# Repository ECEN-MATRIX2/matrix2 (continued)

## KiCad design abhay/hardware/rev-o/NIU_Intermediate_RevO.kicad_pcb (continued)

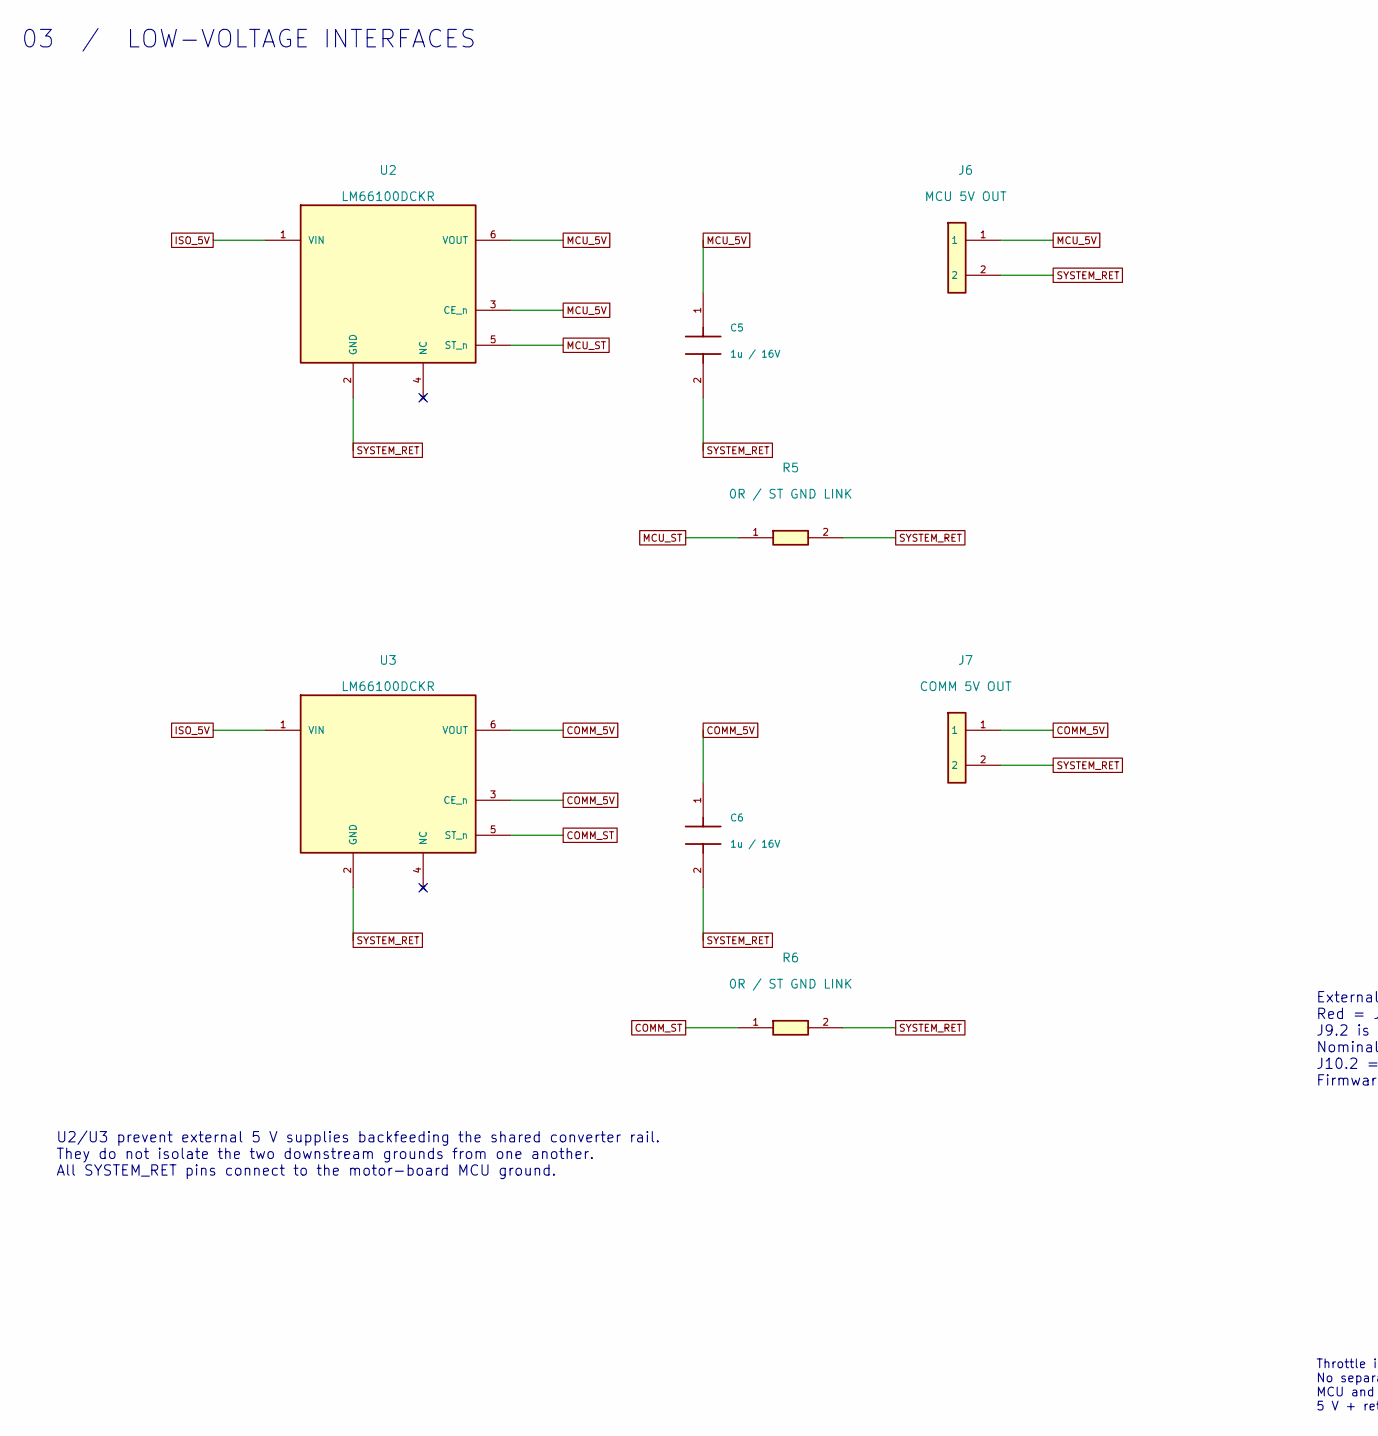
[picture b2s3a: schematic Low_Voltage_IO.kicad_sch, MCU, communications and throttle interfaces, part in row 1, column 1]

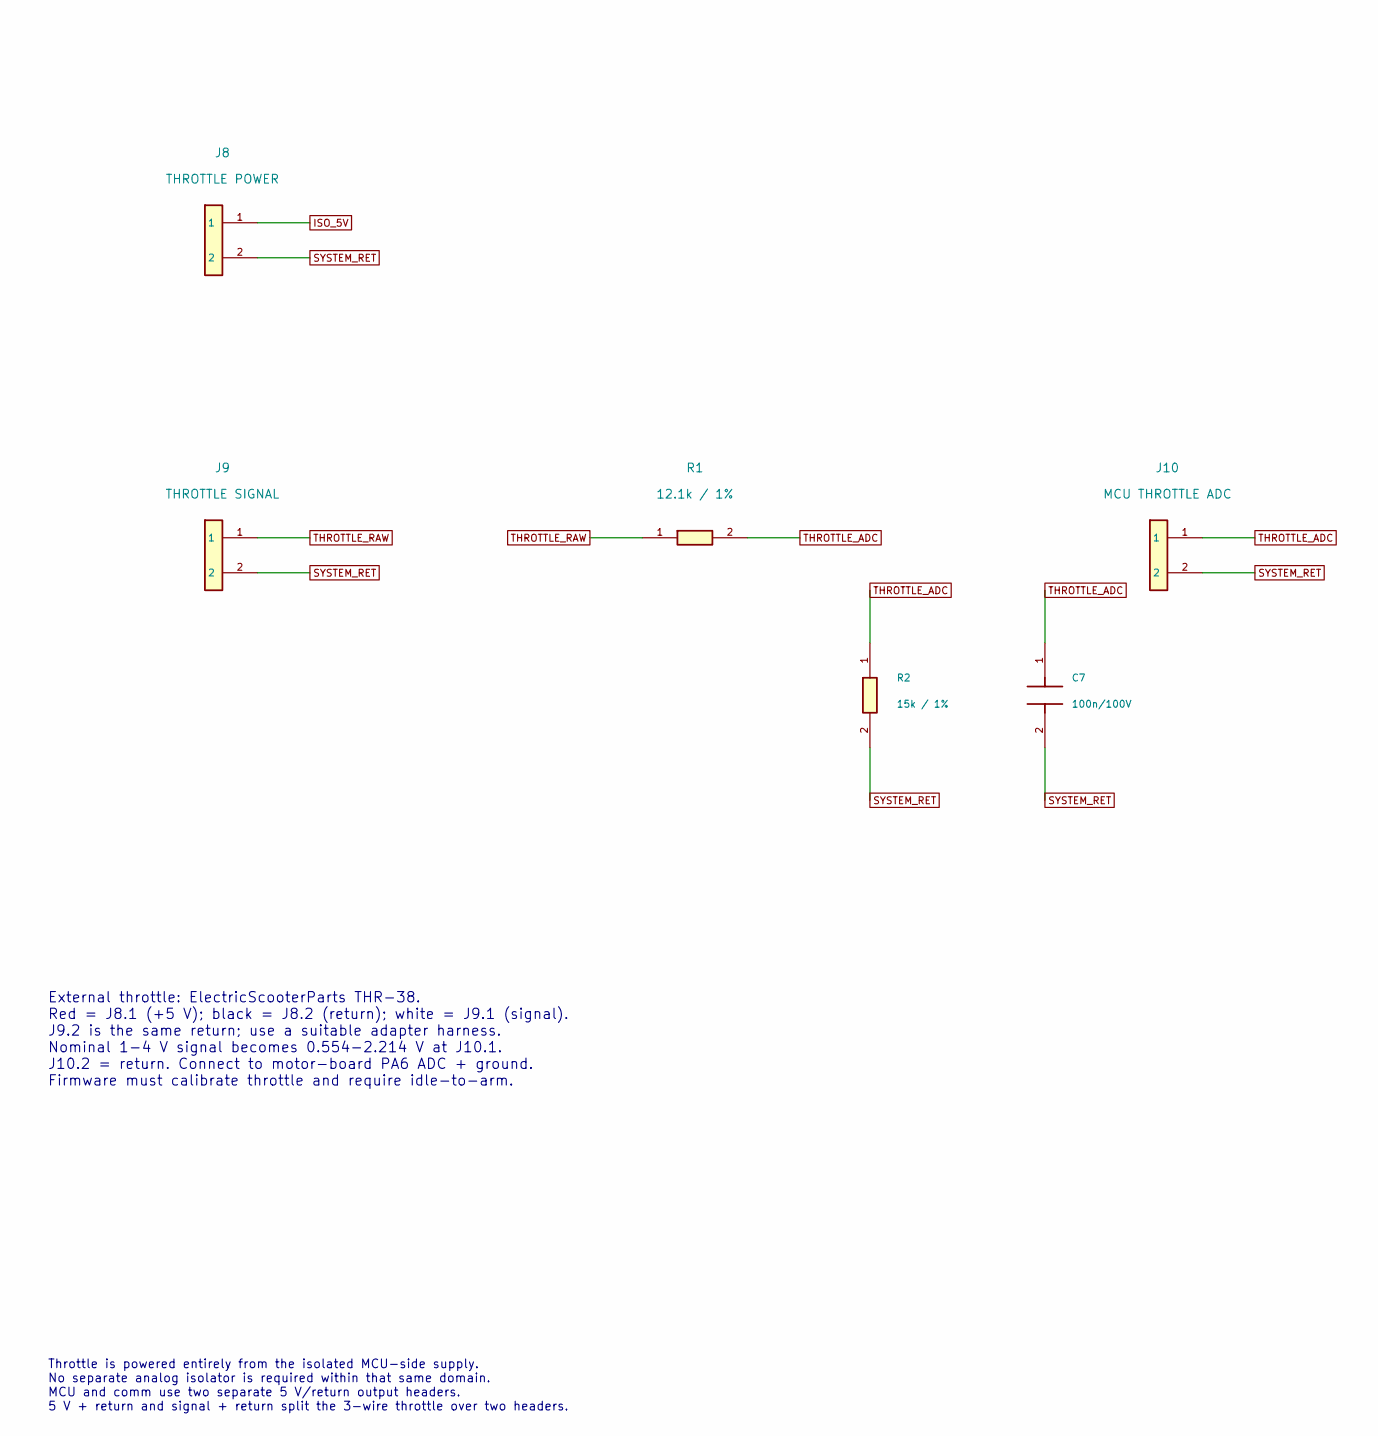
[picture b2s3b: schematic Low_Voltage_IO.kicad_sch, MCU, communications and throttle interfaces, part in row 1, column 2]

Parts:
C5, C6: 1u / 16V; C_0805_2012Metric; Rating X7R 0805, 16V; MPN GRM21BR71C105KA01L; Mouser 81-GRM40X105K16L
C7: 100n/100V; C_0805_2012Metric; Rating X7R, 10%, 0805; MPN C2012X7R2A104K125AA; Mouser 810-C2012X7R2A104K
J6: MCU 5V OUT; PinHeader_1x02_P2.54mm_Vertical; Rating 3A header / LV signals; MPN M20-9990245; Mouser 855-M20-9990245
J7: COMM 5V OUT; PinHeader_1x02_P2.54mm_Vertical; Rating 3A header / LV signals; MPN M20-9990245; Mouser 855-M20-9990245
J8: THROTTLE POWER; PinHeader_1x02_P2.54mm_Vertical; Rating 3A header / LV signals; MPN M20-9990245; Mouser 855-M20-9990245
J9: THROTTLE SIGNAL; PinHeader_1x02_P2.54mm_Vertical; Rating 3A header / LV signals; MPN M20-9990245; Mouser 855-M20-9990245
J10: MCU THROTTLE ADC; PinHeader_1x02_P2.54mm_Vertical; Rating 3A header / LV signals; MPN M20-9990245; Mouser 855-M20-9990245
R1: 12.1k / 1%; R_0805_2012Metric; Rating 1% 0.125W; MPN RC0805FR-0712K1L; Mouser 603-RC0805FR-0712K1L
R2: 15k / 1%; R_0805_2012Metric; Rating 1% 0.125W; MPN RC0805FR-0715KL; Mouser 603-RC0805FR-0715KL
R5, R6: 0R / ST GND LINK; R_0805_2012Metric; Rating 0 ohm configuration link; MPN RC0805JR-070RL; Mouser 603-RC0805JR-070RL
U2, U3: LM66100DCKR; SOT-363_SC-70-6; Rating 1.5-5.5V / 1.5A; MPN LM66100DCKR; Mouser 595-LM66100DCKR

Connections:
COMM_5V: C6.1, J7.1, U3.3 (CE_n), U3.6 (VOUT)
COMM_ST: R6.1, U3.5 (ST_n)
ISO_5V: J8.1, U2.1 (VIN), U3.1 (VIN); also elsewhere on the board
MCU_5V: C5.1, J6.1, U2.3 (CE_n), U2.6 (VOUT)
MCU_ST: R5.1, U2.5 (ST_n)
SYSTEM_RET: C5.2, C6.2, C7.2, J6.2, J7.2, J8.2, J9.2, J10.2, R2.2, R5.2, R6.2, U2.2 (GND), U3.2 (GND); also elsewhere on the board
THROTTLE_ADC: C7.1, J10.1, R1.2, R2.1
THROTTLE_RAW: J9.1, R1.1

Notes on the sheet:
03 / LOW-VOLTAGE INTERFACES
U2/U3 prevent external 5 V supplies backfeeding the shared converter rail. They do not isolate the two downstream grounds from one another. All SYSTEM_RET pins connect to the motor-board MCU ground.
External throttle: ElectricScooterParts THR-38. Red = J8.1 (+5 V); black = J8.2 (return); white = J9.1 (signal). J9.2 is the same return; use a suitable adapter harness. Nominal 1-4 V signal becomes 0.554-2.214 V at J10.1. J10.2 = return. Connect to motor-board PA6 ADC + ground. Firmware must calib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
Throttle is powered entirely from the isolated MCU-side supply. No separate analog isolator is required within that same domain. MCU and comm use two separate 5 V/return output headers. 5 V + return and signal + return split the 3-wire throttle over two headers.

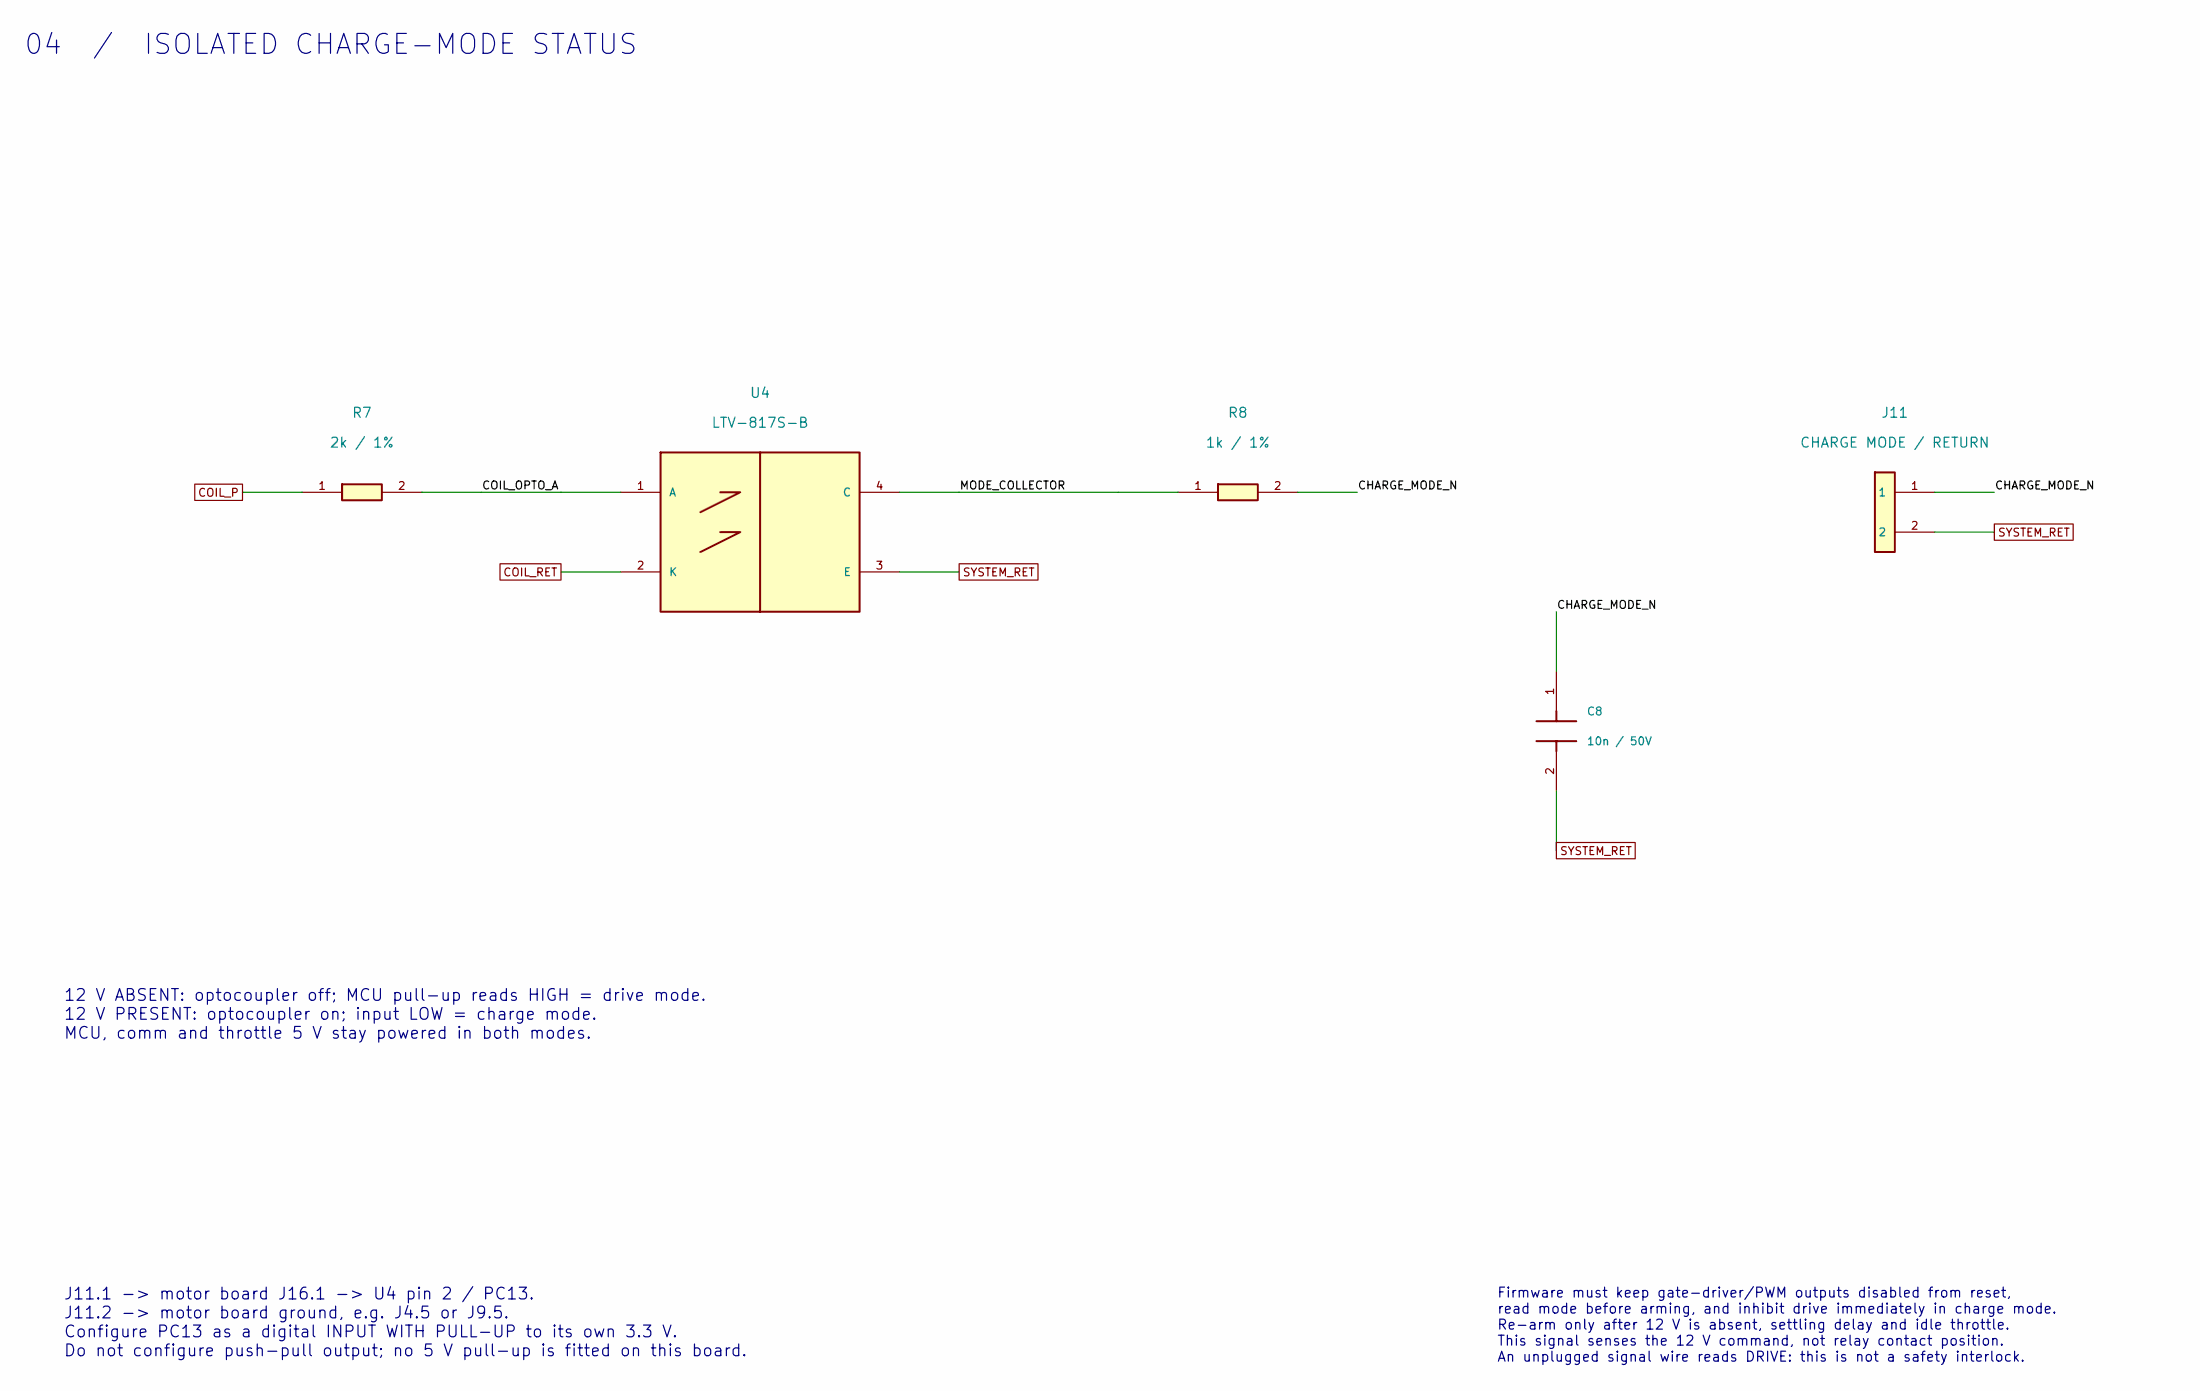
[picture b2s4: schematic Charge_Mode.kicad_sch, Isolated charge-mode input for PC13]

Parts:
C8: 10n / 50V; C_0805_2012Metric; Rating X7R, 10%, 0805; MPN C0805C103K5RACTU; Mouser 80-C0805C103K5R
J11: CHARGE MODE / RETURN; PinHeader_1x02_P2.54mm_Vertical; Rating 3A header / LV signals; MPN M20-9990245; Mouser 855-M20-9990245
R7: 2k / 1%; R_0805_2012Metric; Rating 1% 0.125W; MPN RC0805FR-072KL; Mouser 603-RC0805FR-072KL
R8: 1k / 1%; R_0805_2012Metric; Rating 1% 0.125W; MPN RC0805FR-071KL; Mouser 603-RC0805FR-071KL
U4: LTV-817S-B; SMDIP-4_W9.53mm; Rating Optocoupler; CTR 130-260% at 5mA; MPN LTV-817S-B; Mouser 859-LTV-817S-B

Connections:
/Charge Mode/CHARGE_MODE_N: C8.1, J11.1, R8.2
/Charge Mode/COIL_OPTO_A: R7.2, U4.1 (A)
/Charge Mode/MODE_COLLECTOR: R8.1, U4.4 (C)
COIL_P: R7.1; also elsewhere on the board
COIL_RET: U4.2 (K); also elsewhere on the board
SYSTEM_RET: C8.2, J11.2, U4.3 (E); also elsewhere on the board

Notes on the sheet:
04 / ISOLATED CHARGE-MODE STATUS
12 V ABSENT: optocoupler off; MCU pull-up reads HIGH = drive mode. 12 V PRESENT: optocoupler on; input LOW = charge mode. MCU, comm and throttle 5 V stay powered in both modes.
J11.1 -> motor board J16.1 -> U4 pin 2 / PC13. J11.2 -> motor board ground, e.g. J4.5 or J9.5. Configure PC13 as a digital INPUT WITH PULL-UP to its own 3.3 V. Do not configure push-pull output; no 5 V pull-up is fitted on this board.
Firmware must keep gate-driver/PWM outputs disabled from reset, read mode before arming, and inhibit drive immediately in charge mode. Re-arm only after 12 V is absent, settling delay and idle throttle. This signal senses the 12 V command, not relay contact position. An unplugged signal wire reads 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

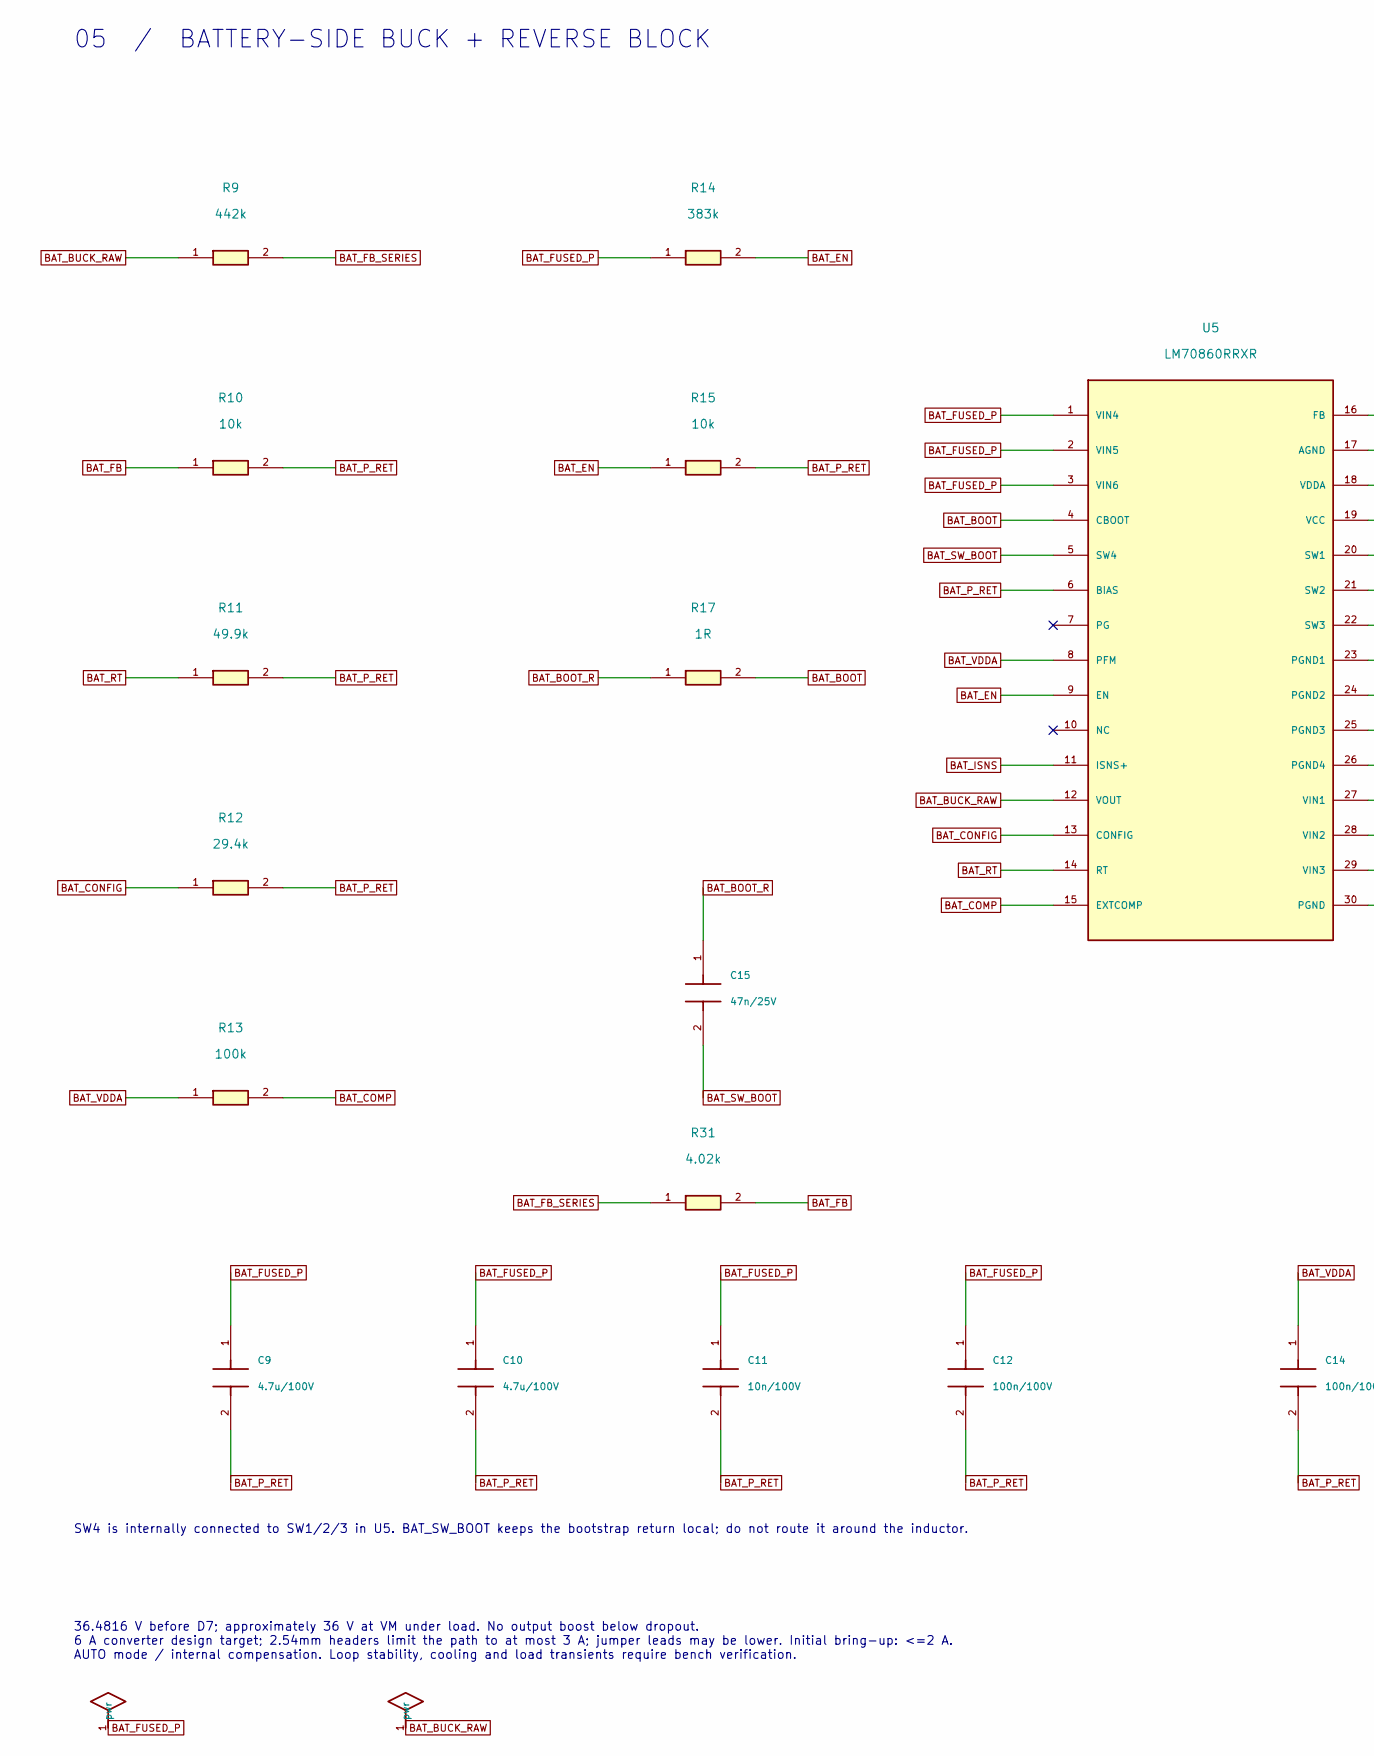
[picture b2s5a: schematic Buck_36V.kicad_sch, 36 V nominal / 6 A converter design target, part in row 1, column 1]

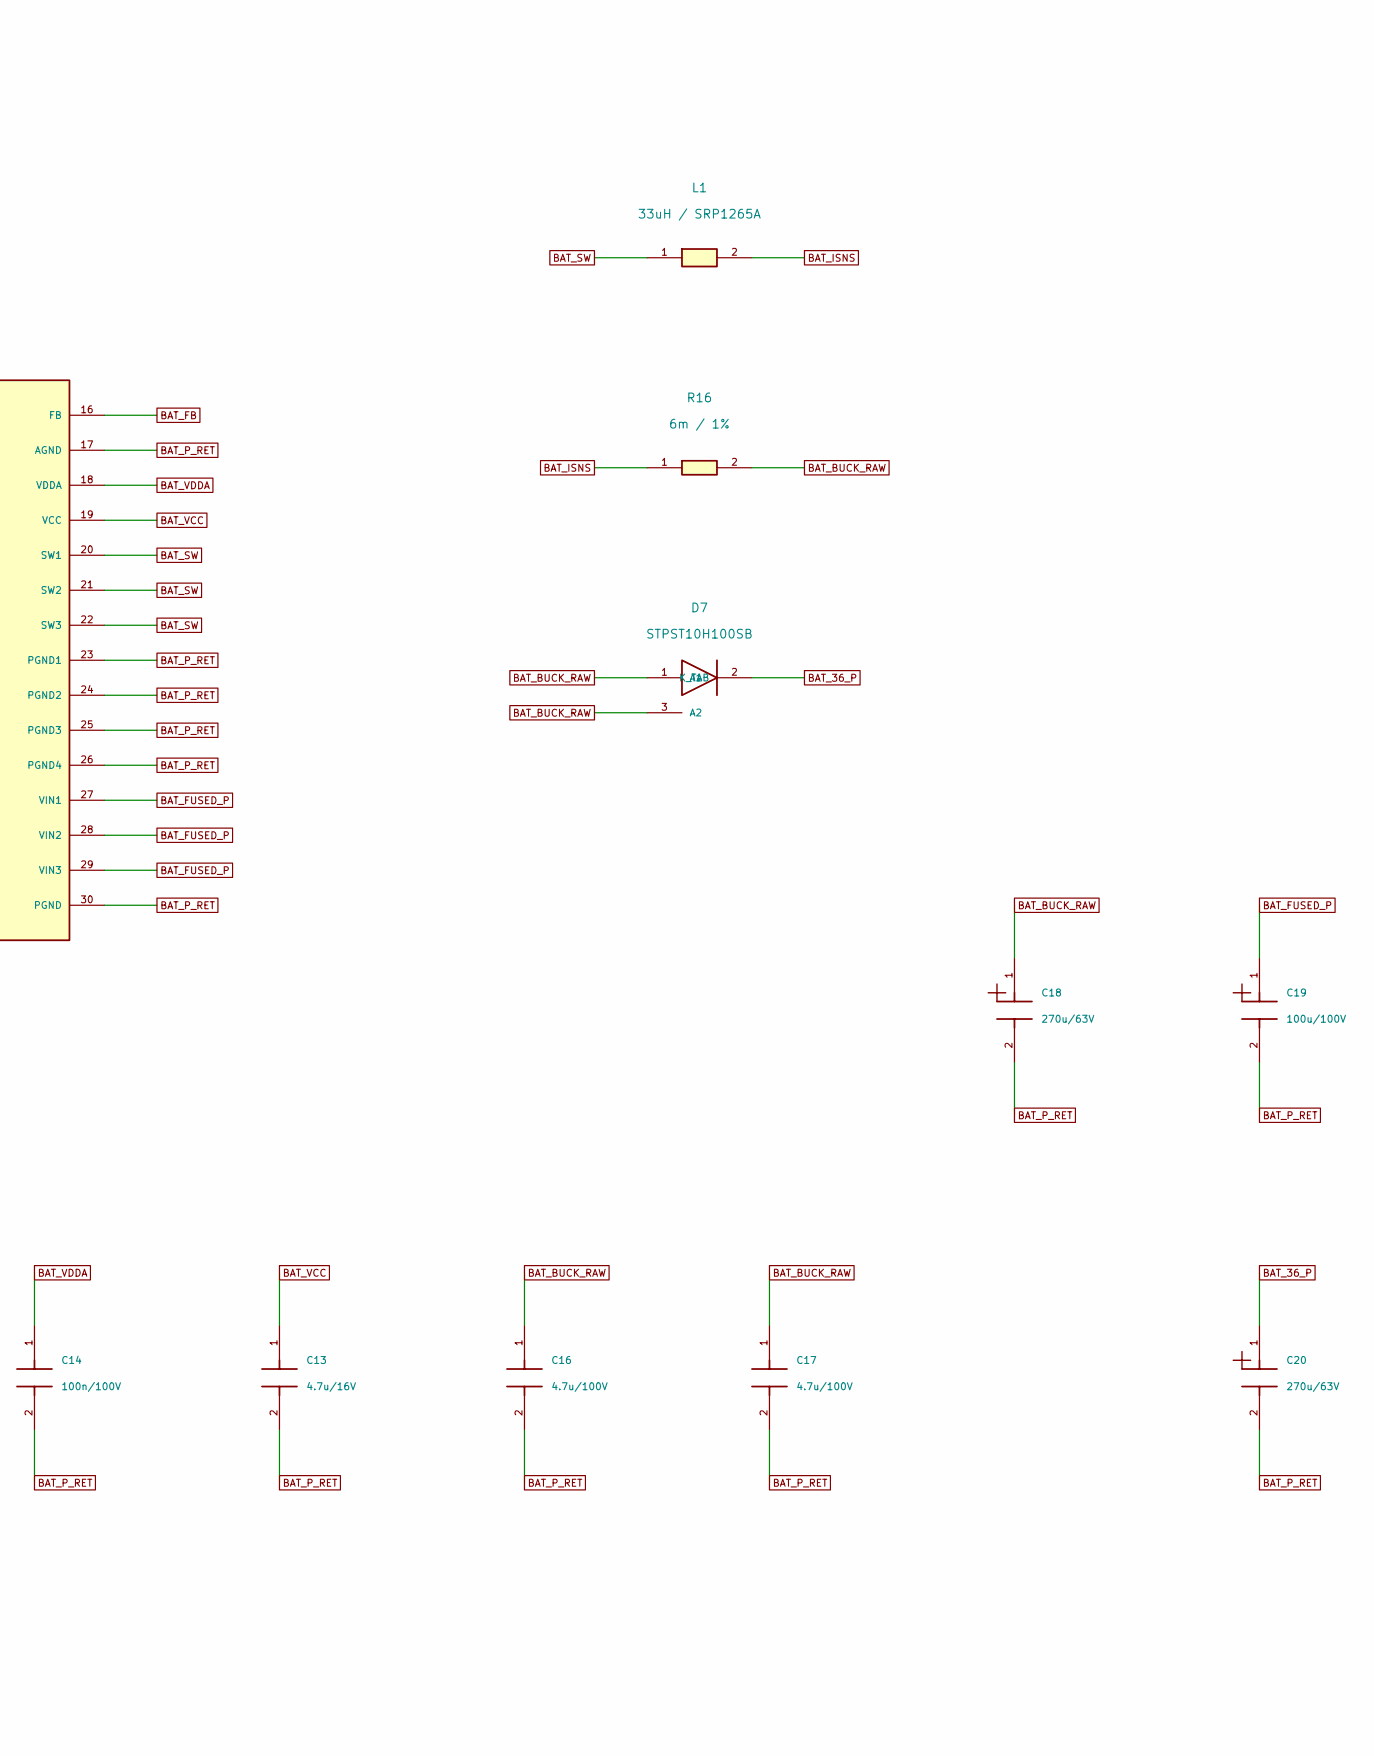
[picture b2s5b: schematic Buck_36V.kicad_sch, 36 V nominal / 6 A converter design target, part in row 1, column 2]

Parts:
C9, C10, C16, C17: 4.7u/100V; TDK_CNC6_1210_Recommended; Rating X7R, 10%, 1210; 3.2 x 2.5 x 2.5 mm; MPN CNC6P1X7R2A475K250AE; Mouser 810-CNC6P1X7R2A475K2
C11: 10n/100V; C_0402_1005Metric; Rating 10nF, 100V, X7S, 0402; MPN C1005X7S2A103K050BB; Mouser 810-C1005X7S2A103K
C12: 100n/100V; C_0603_1608Metric; Rating Verify effective capacitance / ripple c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; MPN GRM188R72A104KA35D; Mouser 81-GRM188R72A104KA35
C13: 4.7u/16V; C_0603_1608Metric; Rating Verify effective capacitance / ripple c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; MPN GRM188R61C475KE11D; Mouser 81-GRM188R61C475KE1D
C14: 100n/100V; C_0603_1608Metric; Rating X7R, 10%, 0603; MPN GRM188R72A104KA35D; Mouser 81-GRM188R72A104KA35
C15: 47n/25V; C_0603_1608Metric; Rating X7R, 10%, 0603; MPN C0603C473K3RACTU; Mouser 80-C0603C473K3R
C18: 270u/63V; CP_Radial_D10.0mm_P5.00mm_H25; Rating 20%; D10 x H25 mm; 5 mm pitch; 0.6 mm l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; MPN EEU-FR1J271L; Mouser 667-EEU-FR1J271L
C19: 100u/100V; CP_Radial_D10.0mm_P5.00mm_H20; Rating Verify effective capacitance / ripple c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; MPN EEU-FR2A101; Mouser 667-EEU-FR2A101
C20: 270u/63V; CP_Radial_D10_P5_H25_PolarityBelow; Rating 20%; D10 x H25 mm; 5 mm pitch; 0.6 mm l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; MPN EEU-FR1J271L; Mouser 667-EEU-FR1J271L
D7: STPST10H100SB; TO-252-3_TabPin2; Rating 100V/10A diode; both anode terminals co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; MPN STPST10H100SB-TR; Mouser 511-STPST10H100SB-TR
L1: 33uH / SRP1265A; Bourns_SRP1265A_13.5x12.5mm; Rating 20%; 8 A Irms; 11 A Isat at 20% drop; D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; MPN SRP1265A-330M; Mouser 652-SRP1265A-330M
R9: 442k; R_0603_1608Metric; Rating 0.1%, 25 ppm/K, 0603; MPN RT0603BRD07442KL; Mouser 603-RT0603BRD07442KL
R10, R15: 10k; R_0603_1608Metric; Rating 0.1% except R17 1%; MPN RT0603BRD0710KL; Mouser 603-RT0603BRD0710KL
R11: 49.9k; R_0603_1608Metric; Rating 0.1% except R17 1%; MPN RT0603BRD0749K9L; Mouser 603-RT0603BRD0749K9L
R12: 29.4k; R_0603_1608Metric; Rating 0.1% except R17 1%; MPN RT0603BRD0729K4L; Mouser 603-RT0603BRD0729K4L
R13: 100k; R_0603_1608Metric; Rating 0.1%, 25 ppm/K, 0603; MPN TNPW0603100KBEEA; Mouser 71-TNPW0603100KBEEA
R14: 383k; R_0603_1608Metric; Rating 0.1% except R17 1%; MPN RT0603BRD07383KL; Mouser 603-RT0603BRD07383KL
R16: 6m / 1%; Vishay_WSL2512_5m_6m9; Rating 1%, 1 W, WSL2512 low-ohm land pattern; MPN WSL25126L000FEA; Mouser 71-WSL25126L000FEA
R17: 1R; R_0603_1608Metric; Rating 0.1% except R17 1%; MPN RC0603FR-071RL; Mouser 603-RC0603FR-071RL
R31: 4.02k; R_0603_1608Metric; Rating 0.1%, 25 ppm/K, 0603; MPN RT0603BRD074K02L; Mouser 603-RT0603BRD074K02L
U5: LM70860RRXR; TI_RRX0029B_6x6; Rating 80V input; 6A target; AUTO; internal co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; MPN LM70860RRXR; Mouser 595-LM70860RRXR

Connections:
BAT_36_P: C20.1, D7.2 (K_TAB); also elsewhere on the board
BAT_BOOT: R17.2, U5.4 (CBOOT)
BAT_BOOT_R: C15.1, R17.1
BAT_BUCK_RAW: C16.1, C17.1, C18.1, D7.1 (A1), D7.3 (A2), R9.1, R16.2, U5.12 (VOUT)
BAT_COMP: R13.2, U5.15 (EXTCOMP)
BAT_CONFIG: R12.1, U5.13 (CONFIG)
BAT_EN: R14.2, R15.1, U5.9 (EN)
BAT_FB: R10.1, R31.2, U5.16 (FB)
BAT_FB_SERIES: R9.2, R31.1
BAT_FUSED_P: C9.1, C10.1, C11.1, C12.1, C19.1, R14.1, U5.1 (VIN4), U5.2 (VIN5), U5.3 (VIN6), U5.27 (VIN1), U5.28 (VIN2), U5.29 (VIN3); also elsewhere on the board
BAT_ISNS: L1.2, R16.1, U5.11 (ISNS+)
BAT_P_RET: C9.2, C10.2, C11.2, C12.2, C13.2, C14.2, C16.2, C17.2, C18.2, C19.2, C20.2, R10.2, R11.2, R12.2, R15.2, U5.6 (BIAS), U5.17 (AGND), U5.23 (PGND1), U5.24 (PGND2), U5.25 (PGND3), U5.26 (PGND4), U5.30 (PGND); also elsewhere on the board
BAT_RT: R11.1, U5.14 (RT)
BAT_SW: L1.1, U5.20 (SW1), U5.21 (SW2), U5.22 (SW3)
BAT_SW_BOOT: C15.2, U5.5 (SW4)
BAT_VCC: C13.1, U5.19 (VCC)
BAT_VDDA: C14.1, R13.1, U5.8 (PFM), U5.18 (VDDA)

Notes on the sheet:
05 / BATTERY-SIDE BUCK + REVERSE BLOCK
36.4816 V before D7; approximately 36 V at VM under load. No output boost below dropout. 6 A converter design target; 2.54mm headers limit the path to at most 3 A; jumper leads may be lower. Initial bring-up: <=2 A. AUTO mode / internal compensation. Loop stability, cooling and load transients requ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
SW4 is internally connected to SW1/2/3 in U5. BAT_SW_BOOT keeps the bootstrap return local; do not route it around the inductor.

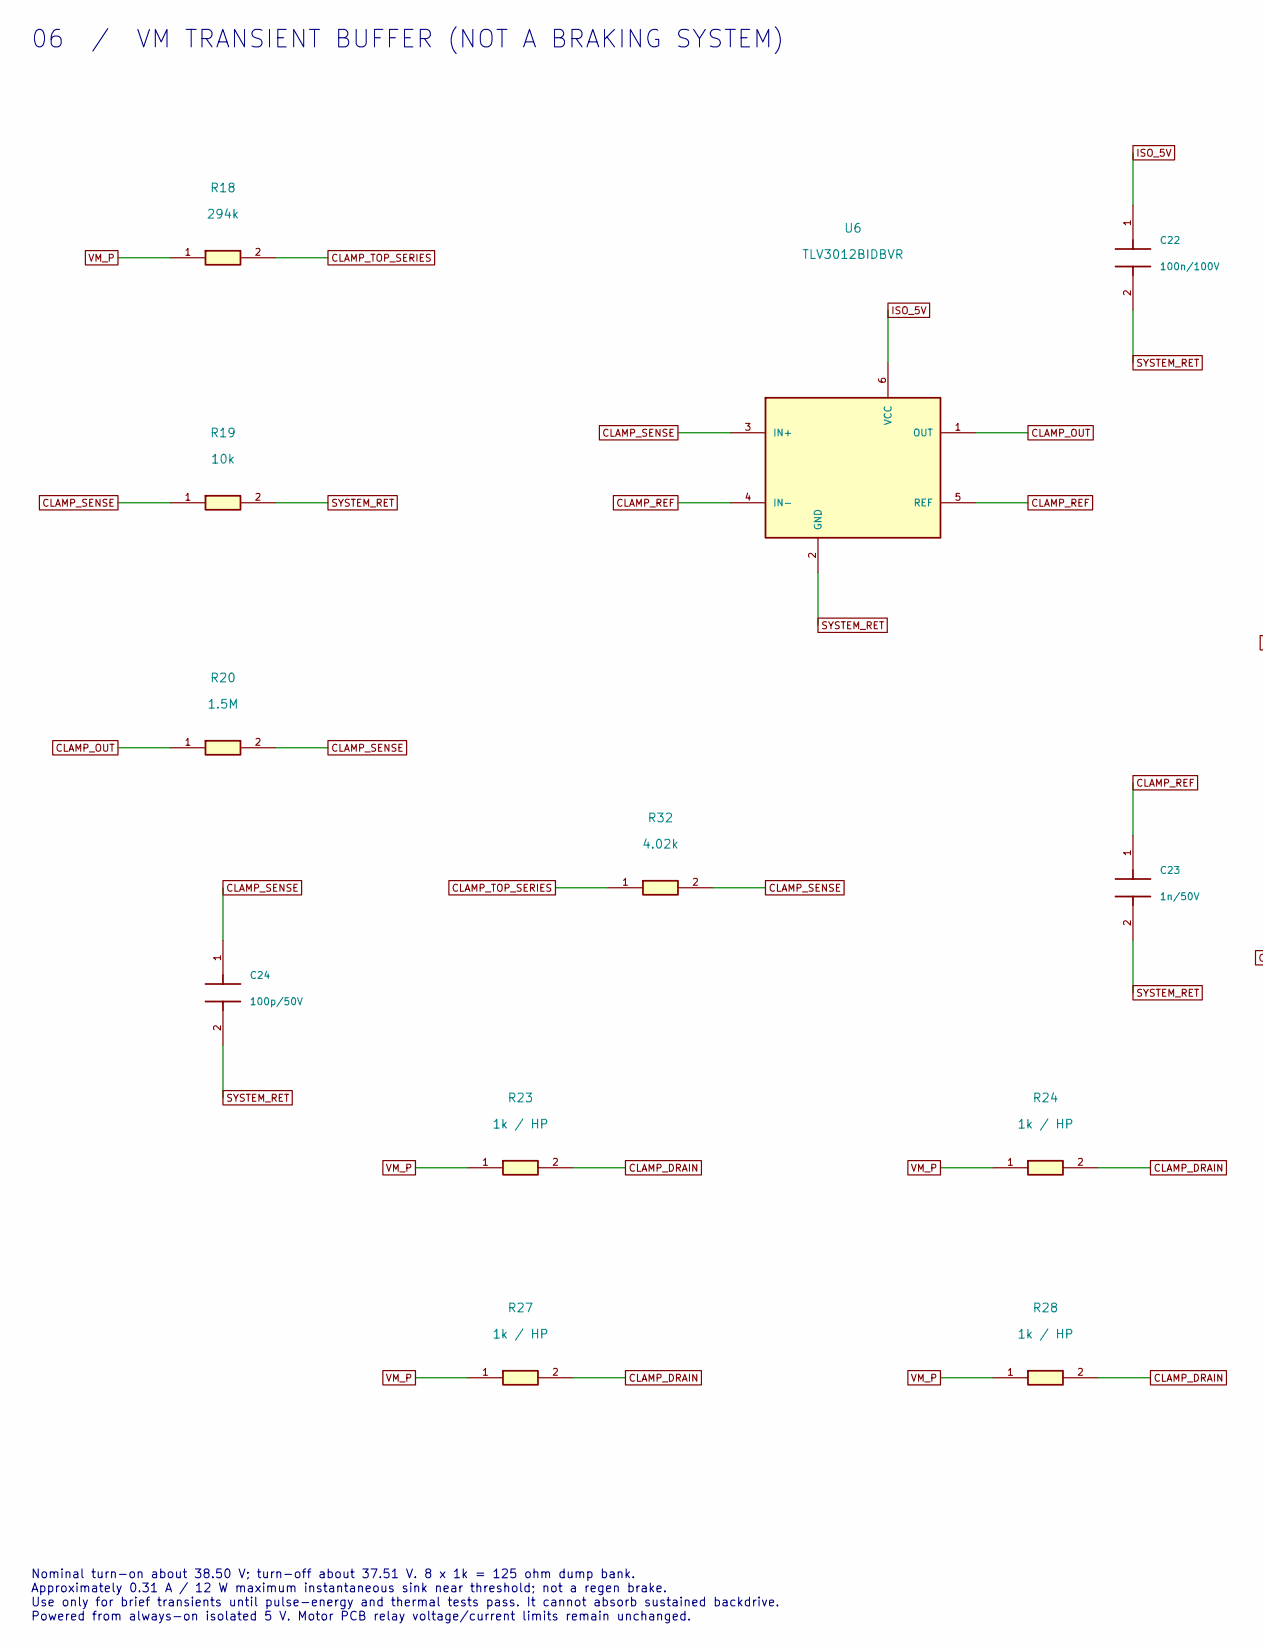
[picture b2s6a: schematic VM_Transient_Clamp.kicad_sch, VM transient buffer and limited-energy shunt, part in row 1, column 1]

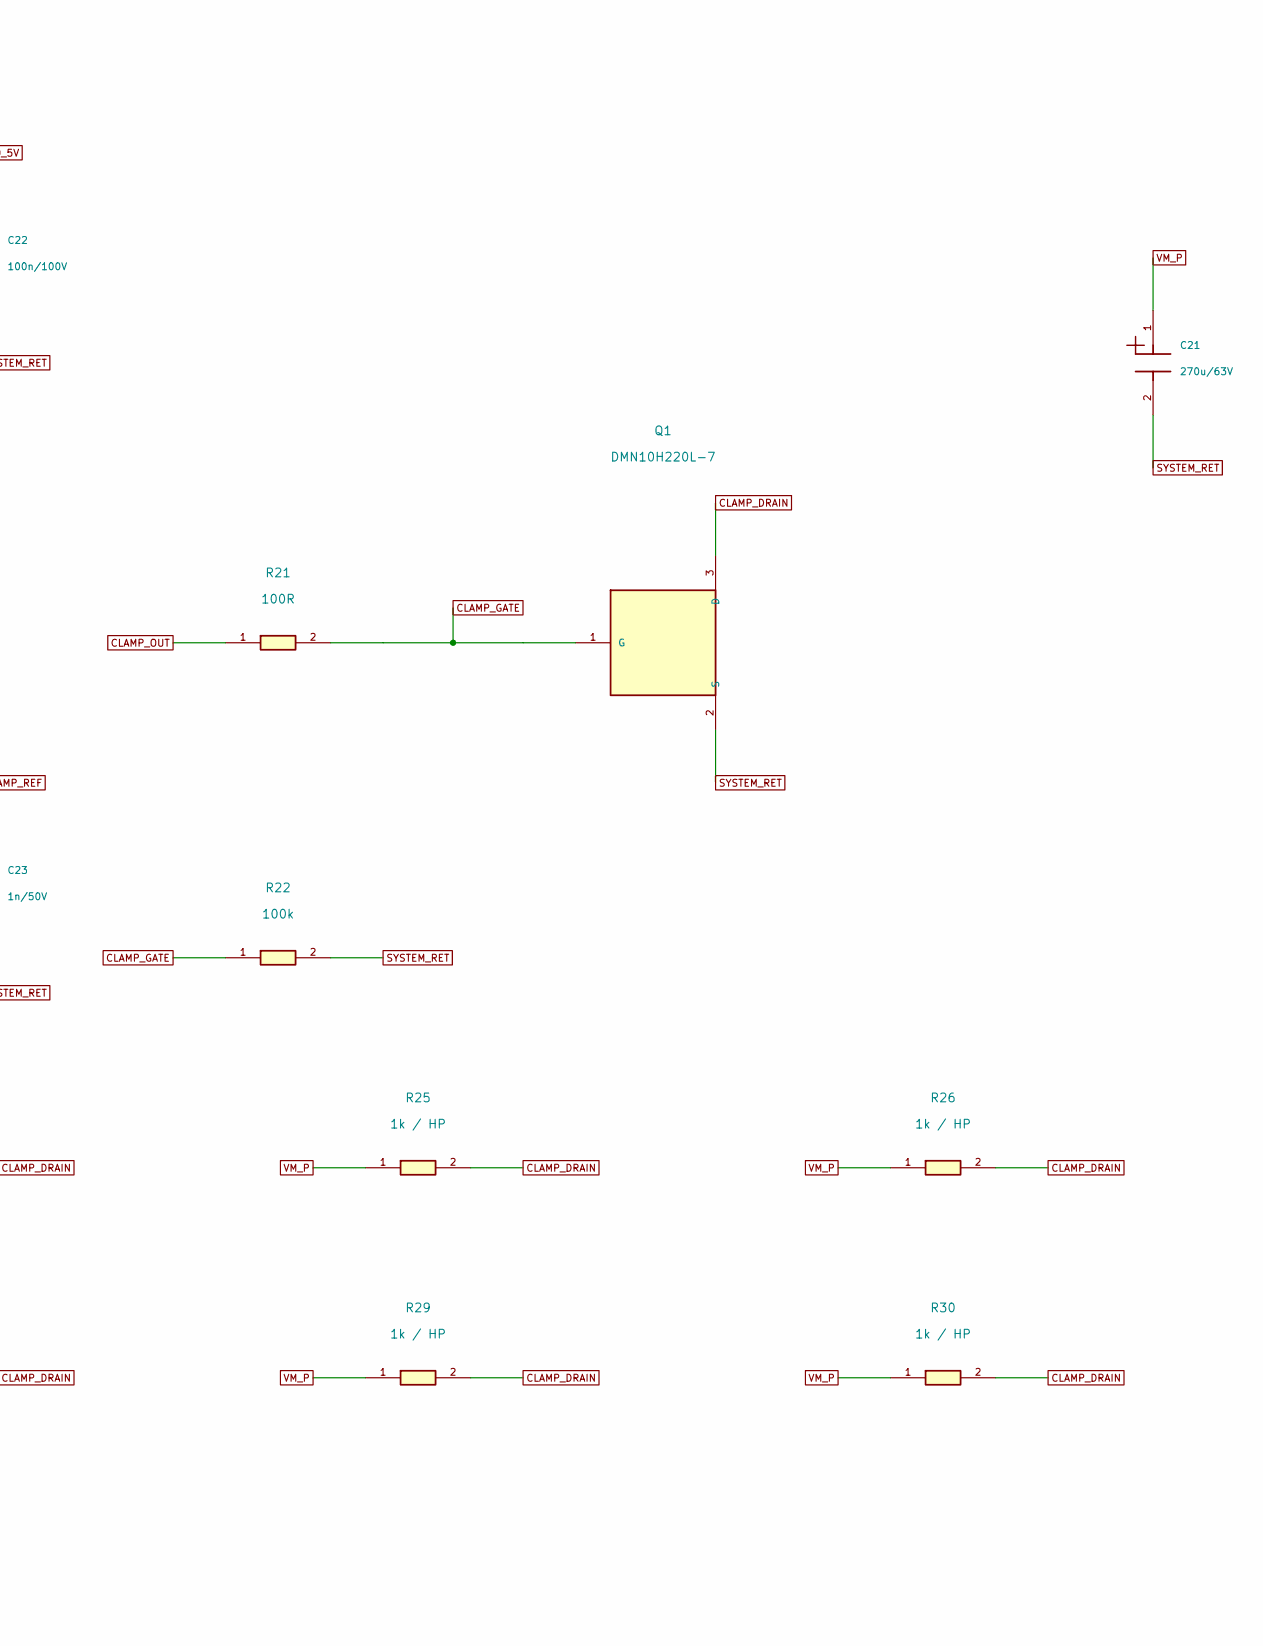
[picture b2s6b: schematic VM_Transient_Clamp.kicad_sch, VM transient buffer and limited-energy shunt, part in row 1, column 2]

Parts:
C21: 270u/63V; CP_Radial_D10.0mm_P5.00mm_H25; Rating 20%; D10 x H25 mm; 5 mm pitch; 0.6 mm l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; MPN EEU-FR1J271L; Mouser 667-EEU-FR1J271L
C22: 100n/100V; C_0603_1608Metric; Rating X7R, 10%, 0603; MPN GRM188R72A104KA35D; Mouser 81-GRM188R72A104KA35
C23: 1n/50V; C_0603_1608Metric; Rating C0G, 5%, 0603; 1.6 x 0.8 x 0.8 mm nomin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; MPN C0603C102J5GACTU; Mouser 80-C0603C102J5G
C24: 100p/50V; C_0603_1608Metric; Rating C21 10mm diameter 5mm pitch; others cer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; MPN GRM1885C1H101JA01D; Mouser 81-GRM39C101J50
Q1: DMN10H220L-7; SOT-23; Rating 100V; Rds max 0.25ohm at 4.5V; MPN DMN10H220L-7; Mouser 621-DMN10H220L-7
R18: 294k; R_0603_1608Metric; Rating 0.1%, 25 ppm/K, 0603; MPN TNPW0603294KBEEN; Mouser 71-TNPW0603294KBEEN
R19: 10k; R_0603_1608Metric; Rating 0.1% R18-R20; 1% others; MPN RT0603BRD0710KL; Mouser 603-RT0603BRD0710KL
R20: 1.5M; R_0603_1608Metric; Rating 0.1%, 25 ppm/K, 0603; MPN MCT0603MD1504BP500; Mouser 594-MCT0603MD1504BP5
R21: 100R; R_0603_1608Metric; Rating 0.1% R18-R20; 1% others; MPN RC0603FR-07100RL; Mouser 603-RC0603FR-07100RL
R22: 100k; R_0603_1608Metric; Rating 0.1% R18-R20; 1% others; MPN RC0603FR-07100KL; Mouser 603-RC0603FR-07100KL
R23, R24, R25, R26, R27, R28, R29, R30: 1k / HP; R_2512_6332Metric; Rating 1.5W at70C / 2W terminal <=105C; MPN CRCW25121K00FKEGHP; Mouser 71-CRCW25121K00FKEGH
R32: 4.02k; R_0603_1608Metric; Rating 0.1%, 25 ppm/K, 0603; MPN RT0603BRD074K02L; Mouser 603-RT0603BRD074K02L
U6: TLV3012BIDBVR; SOT-23-6; Rating 1.242V ref; push-pull; POR low; MPN TLV3012BIDBVR; Mouser 595-TLV3012BIDBVR

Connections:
CLAMP_DRAIN: Q1.3 (D), R23.2, R24.2, R25.2, R26.2, R27.2, R28.2, R29.2, R30.2
CLAMP_GATE: Q1.1 (G), R21.2, R22.1
CLAMP_OUT: R20.1, R21.1, U6.1 (OUT)
CLAMP_REF: C23.1, U6.4 (IN-), U6.5 (REF)
CLAMP_SENSE: C24.1, R19.1, R20.2, R32.2, U6.3 (IN+)
CLAMP_TOP_SERIES: R18.2, R32.1
ISO_5V: C22.1, U6.6 (VCC); also elsewhere on the board
SYSTEM_RET: C21.2, C22.2, C23.2, C24.2, Q1.2 (S), R19.2, R22.2, U6.2 (GND); also elsewhere on the board
VM_P: C21.1, R18.1, R23.1, R24.1, R25.1, R26.1, R27.1, R28.1, R29.1, R30.1; also elsewhere on the board

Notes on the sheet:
06 / VM TRANSIENT BUFFER (NOT A BRAKING SYSTEM)
Nominal turn-on about 38.50 V; turn-off about 37.51 V. 8 x 1k = 125 ohm dump bank. Approximately 0.31 A / 12 W maximum instantaneous sink near threshold; not a regen brake. Use only for brief transients until pulse-energy and thermal tests pass. It cannot absorb sustained backdrive. Powered from al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
